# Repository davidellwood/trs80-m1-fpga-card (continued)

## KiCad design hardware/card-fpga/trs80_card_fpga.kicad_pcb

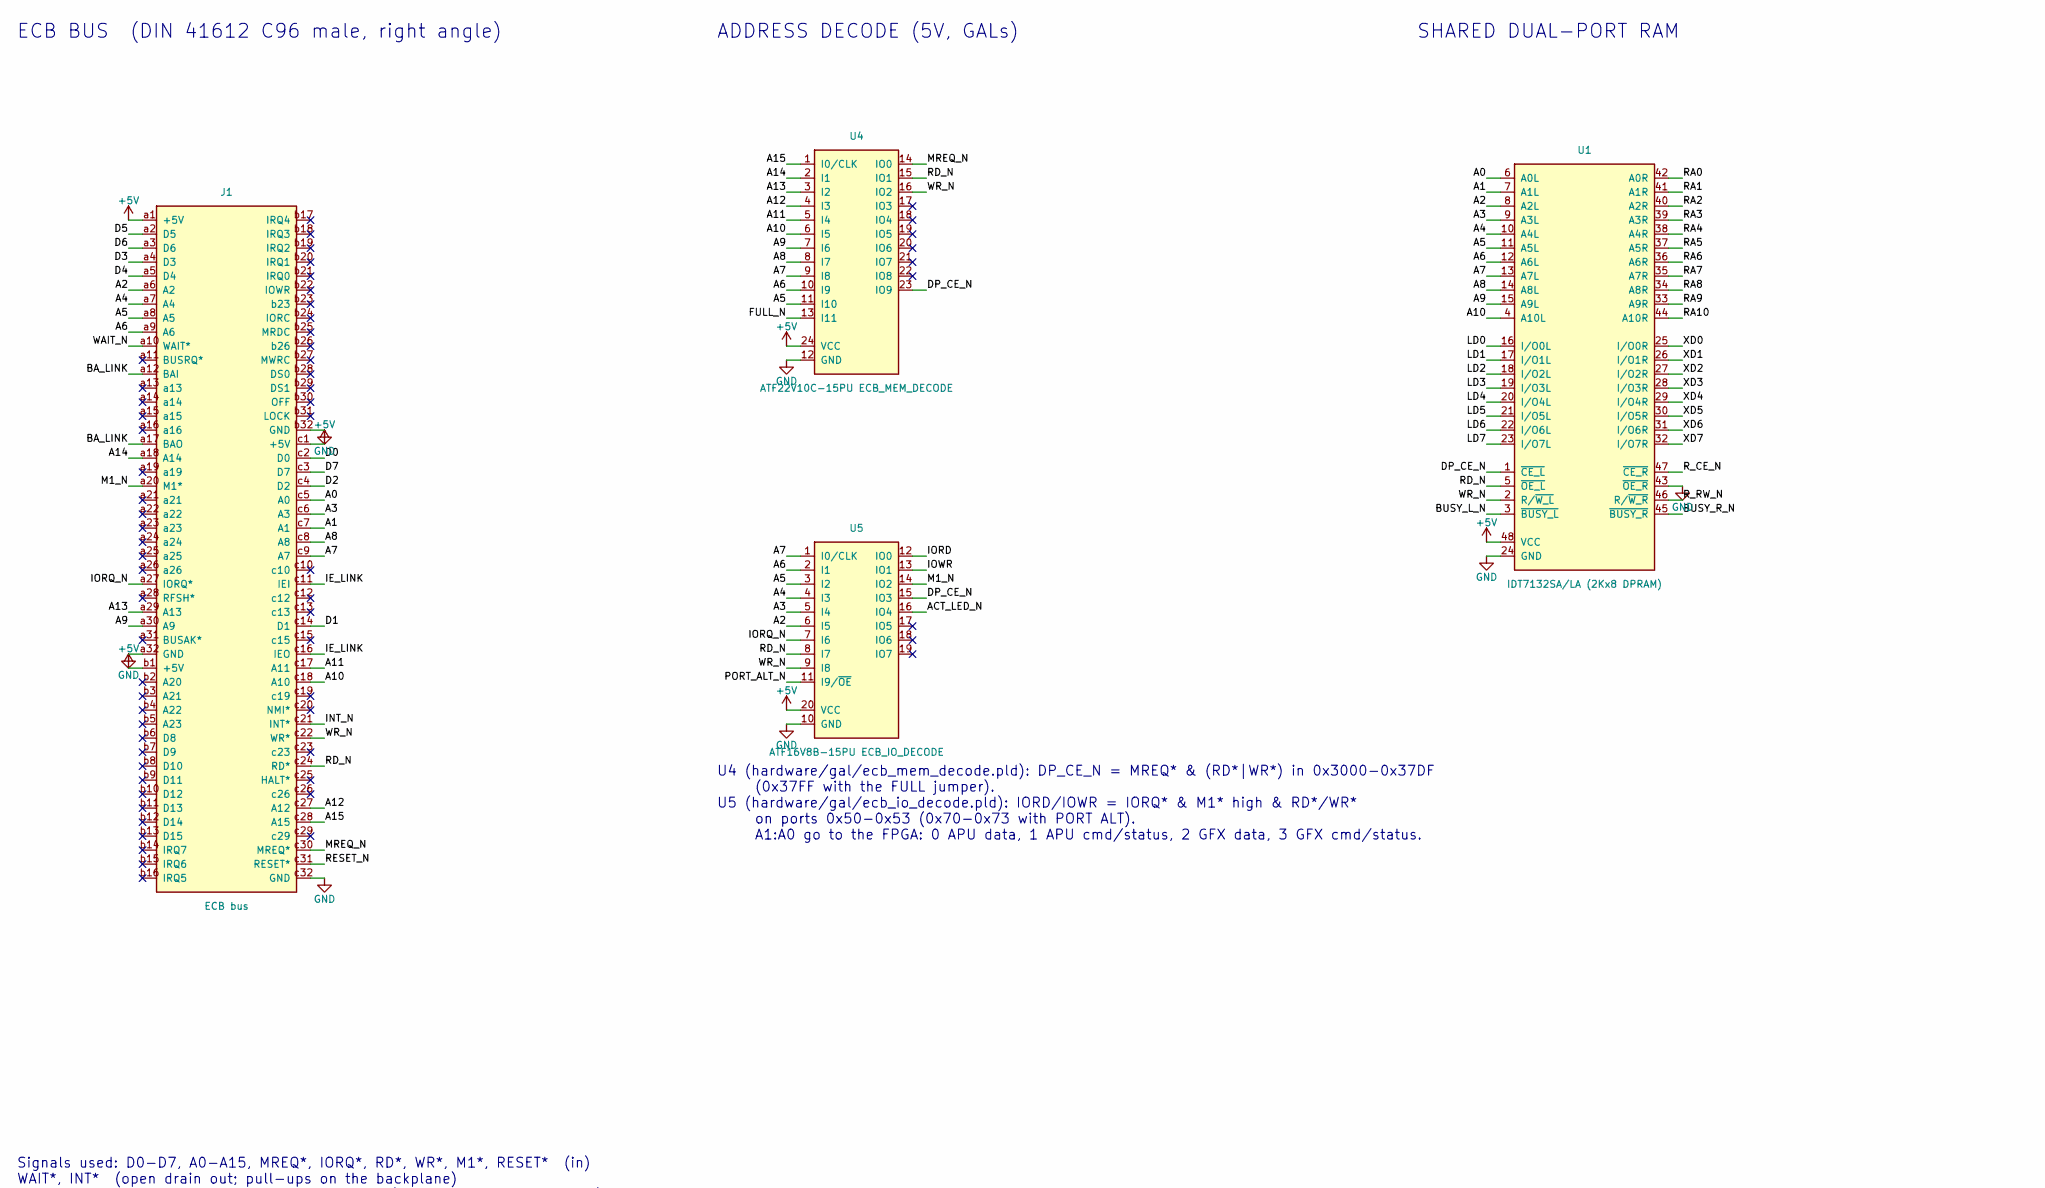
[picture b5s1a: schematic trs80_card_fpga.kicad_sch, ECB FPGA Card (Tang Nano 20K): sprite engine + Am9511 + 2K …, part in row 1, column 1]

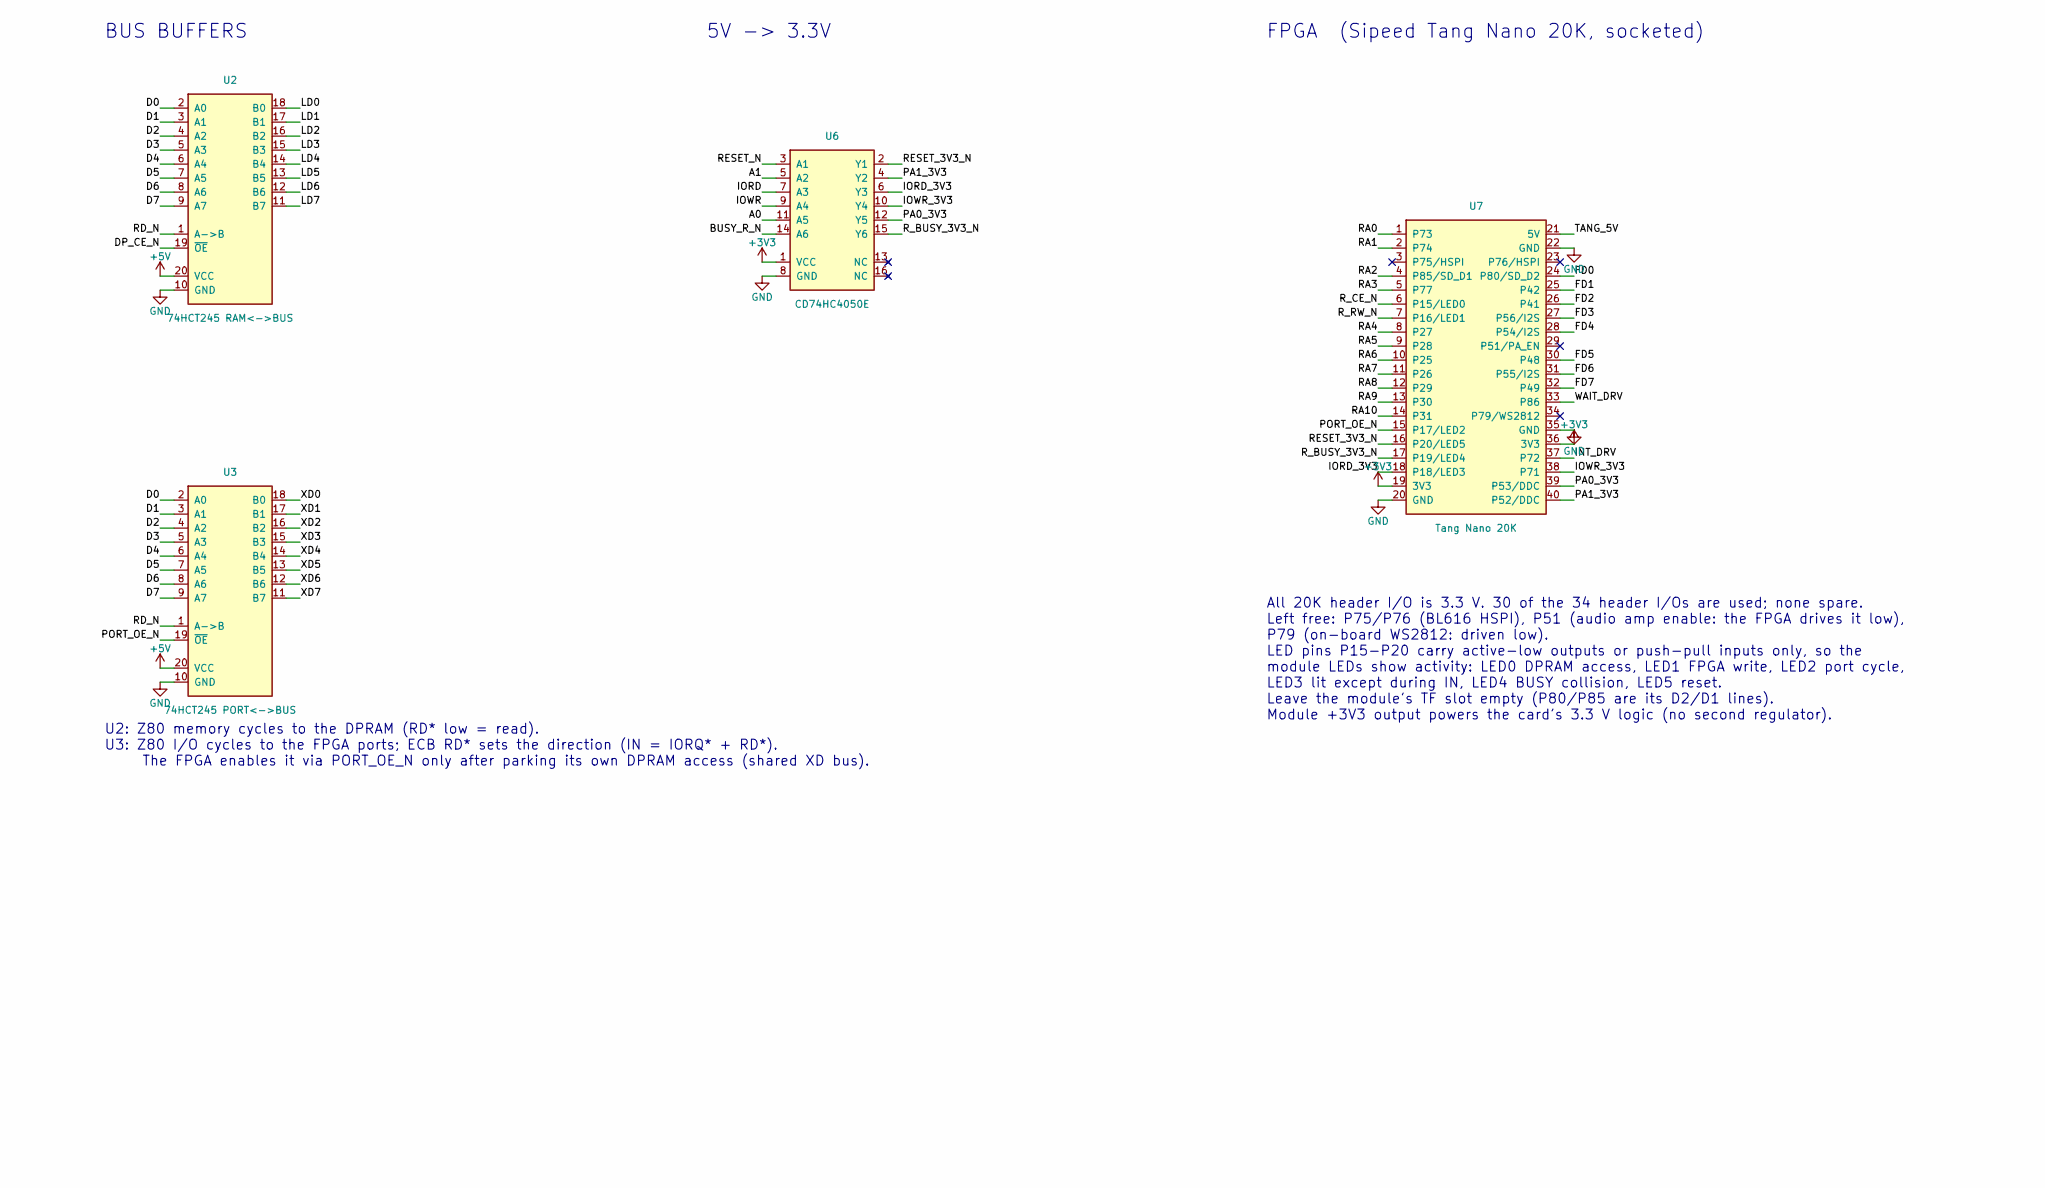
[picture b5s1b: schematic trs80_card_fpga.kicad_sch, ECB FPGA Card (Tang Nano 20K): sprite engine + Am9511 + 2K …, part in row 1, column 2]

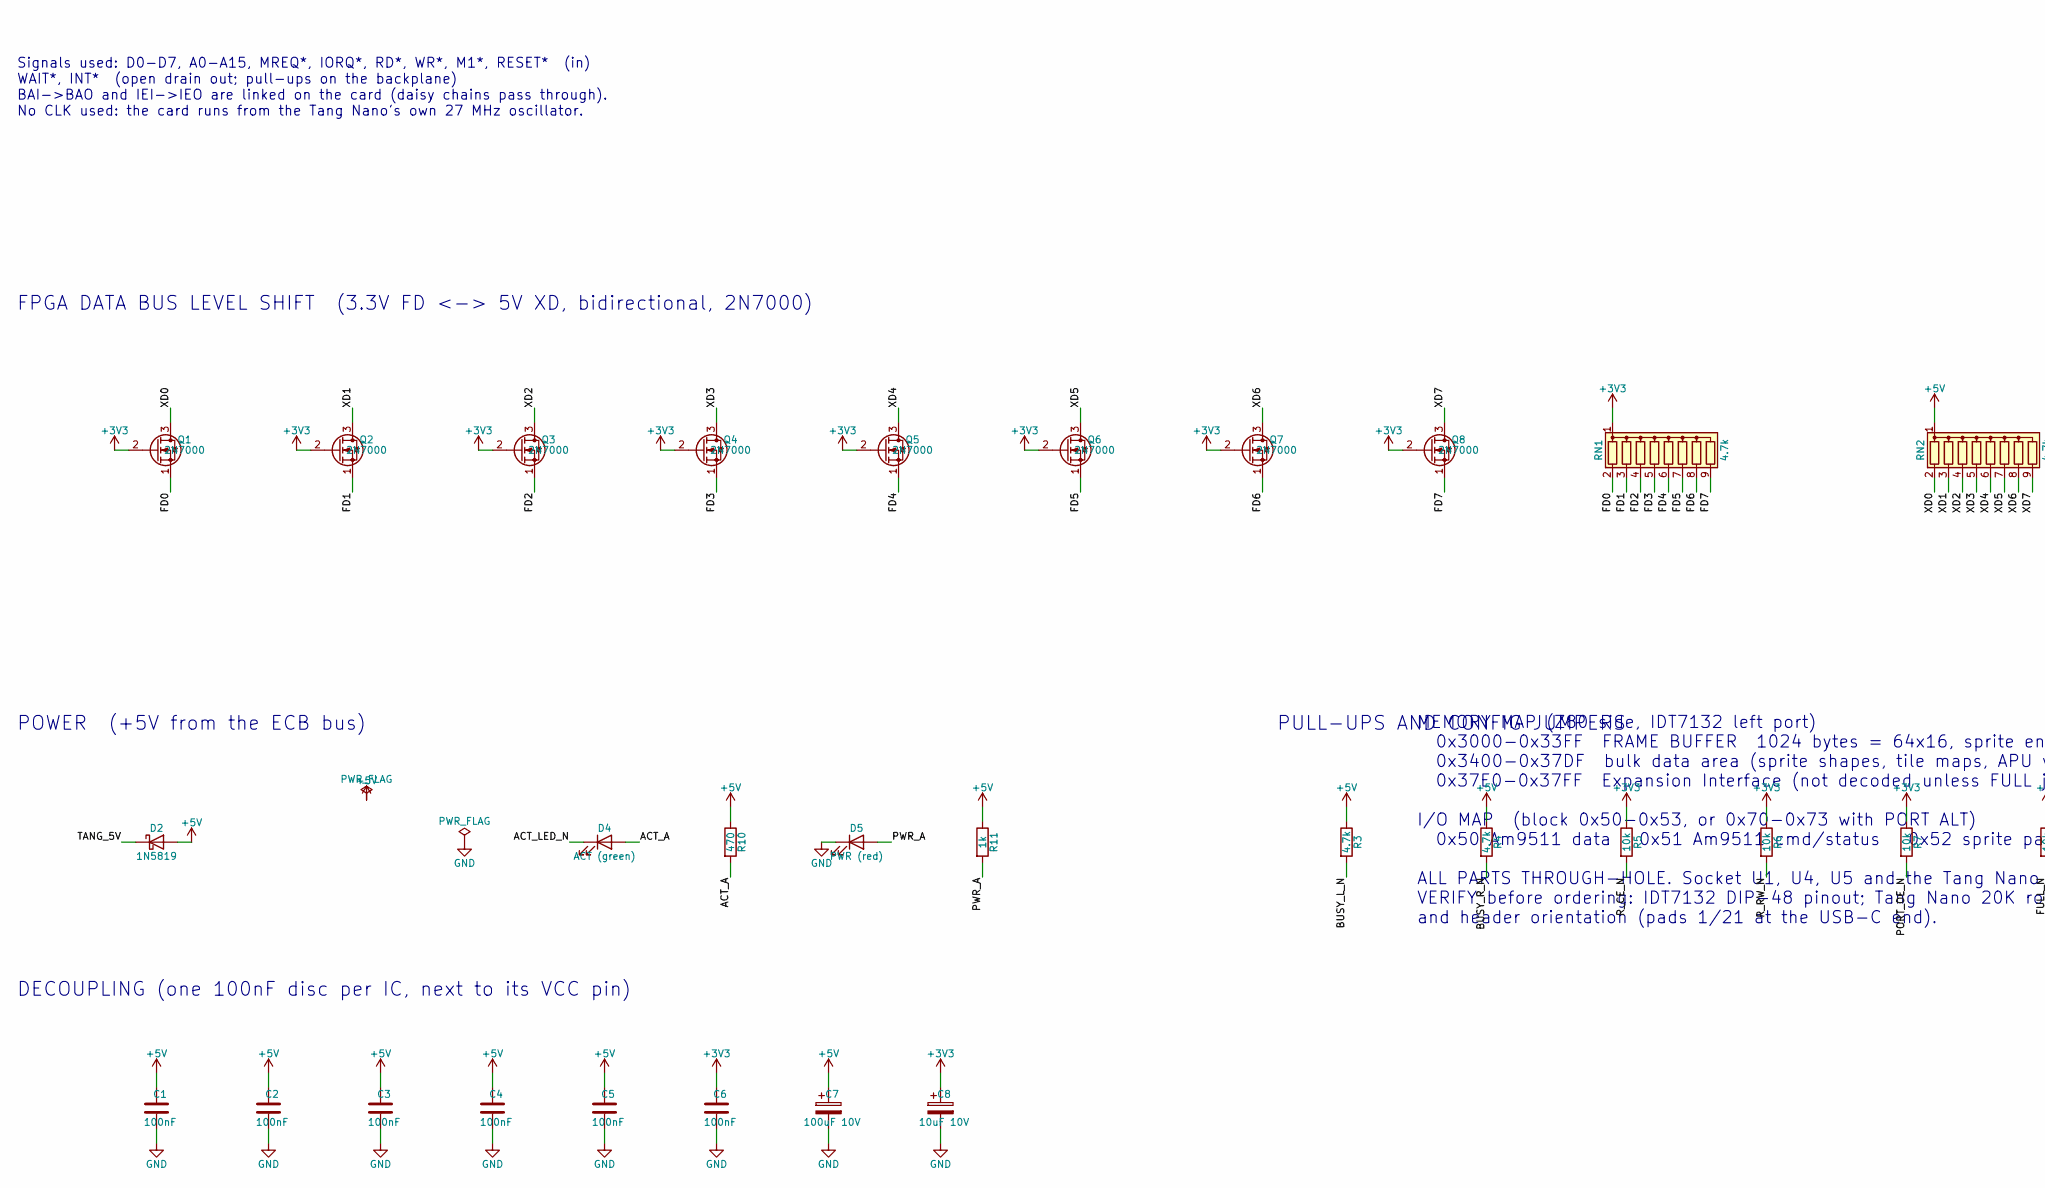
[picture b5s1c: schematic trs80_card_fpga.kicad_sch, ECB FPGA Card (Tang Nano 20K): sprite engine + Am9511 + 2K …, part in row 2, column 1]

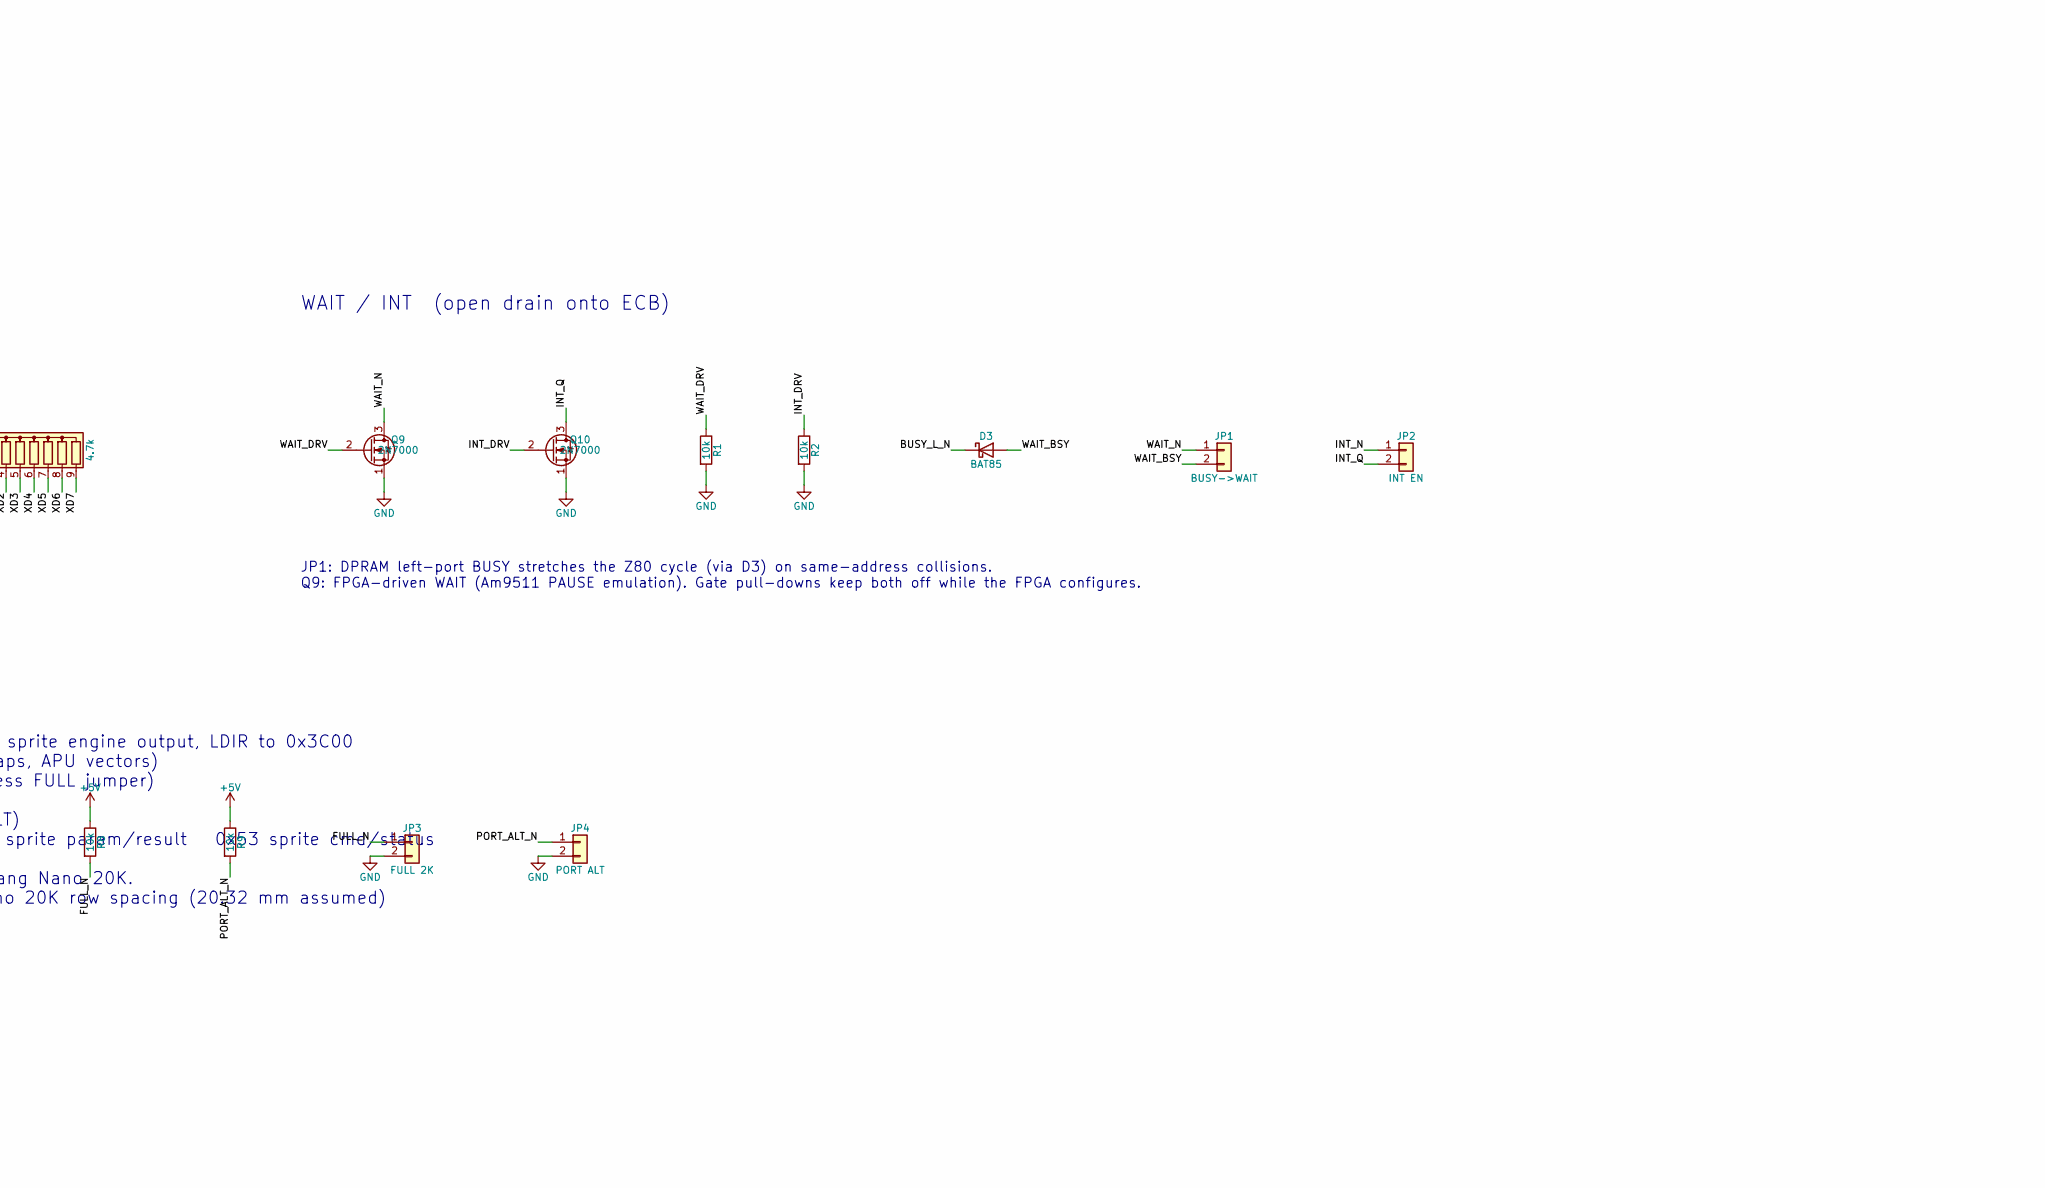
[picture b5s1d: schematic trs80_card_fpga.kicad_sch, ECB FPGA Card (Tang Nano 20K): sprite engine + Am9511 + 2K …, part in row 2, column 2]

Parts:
C1, C2, C3, C4, C5, C6: 100nF; C_Disc_D5.0mm_W2.5mm_P5.00mm
C7: 100uF 10V; CP_Radial_D6.3mm_P2.50mm
C8: 10uF 10V; CP_Radial_D6.3mm_P2.50mm
D2: 1N5819; D_DO-41_SOD81_P10.16mm_Horizontal
D3: BAT85; D_DO-35_SOD27_P7.62mm_Horizontal
D4: ACT (green); LED_D3.0mm
D5: PWR (red); LED_D3.0mm
J1: ECB bus; DIN41612_C_3x32_Male_Horizontal_THT
JP1: BUSY->WAIT; PinHeader_1x02_P2.54mm_Vertical
JP2: INT EN; PinHeader_1x02_P2.54mm_Vertical
JP3: FULL 2K; PinHeader_1x02_P2.54mm_Vertical
JP4: PORT ALT; PinHeader_1x02_P2.54mm_Vertical
Q1, Q2, Q3, Q4, Q5, Q6, Q7, Q8, Q9, Q10: 2N7000; TO-92_Inline_Wide
R1, R2, R5, R6, R7, R8, R9: 10k; R_Axial_DIN0207_L6.3mm_D2.5mm_P10.16mm_Horizontal
R3, R4: 4.7k; R_Axial_DIN0207_L6.3mm_D2.5mm_P10.16mm_Horizontal
R10: 470; R_Axial_DIN0207_L6.3mm_D2.5mm_P10.16mm_Horizontal
R11: 1k; R_Axial_DIN0207_L6.3mm_D2.5mm_P10.16mm_Horizontal
RN1, RN2: 4.7k; R_Array_SIP9
U1: IDT7132SA/LA (2Kx8 DPRAM); DIP-48_W15.24mm_Socket
U2: 74HCT245 RAM<->BUS; DIP-20_W7.62mm
U3: 74HCT245 PORT<->BUS; DIP-20_W7.62mm
U4: ATF22V10C-15PU ECB_MEM_DECODE; DIP-24_W7.62mm_Socket
U5: ATF16V8B-15PU ECB_IO_DECODE; DIP-20_W7.62mm_Socket
U6: CD74HC4050E; DIP-16_W7.62mm
U7: Tang Nano 20K; TangNano20K_2x20_W20.32mm

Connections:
+3V3: C6.1, C8.1, Q1.2 (G), Q2.2 (G), Q3.2 (G), Q4.2 (G), Q5.2 (G), Q6.2 (G), Q7.2 (G), Q8.2 (G), R5.1, R6.1, R7.1, RN1.1 (common), U6.1 (VCC), U7.19 (3V3), U7.36 (3V3)
+5V: C1.1, C2.1, C3.1, C4.1, C5.1, C7.1, D2.2 (A), J1.a1 (+5V), J1.b1 (+5V), J1.c1 (+5V), R3.1, R4.1, R8.1, R9.1, R10.1, R11.1, RN2.1 (common), U1.48 (VCC), U2.20 (VCC), U3.20 (VCC), U4.24 (VCC), U5.20 (VCC)
/A0: J1.c5 (A0), U1.6 (A0L), U6.11 (A5)
/A1: J1.c7 (A1), U1.7 (A1L), U6.5 (A2)
/A2: J1.a6 (A2), U1.8 (A2L), U5.6 (I5)
/A3: J1.c6 (A3), U1.9 (A3L), U5.5 (I4)
/A4: J1.a7 (A4), U1.10 (A4L), U5.4 (I3)
/A5: J1.a8 (A5), U1.11 (A5L), U4.11 (I10), U5.3 (I2)
/A6: J1.a9 (A6), U1.12 (A6L), U4.10 (I9), U5.2 (I1)
/A7: J1.c9 (A7), U1.13 (A7L), U4.9 (I8), U5.1 (I0/CLK)
/A8: J1.c8 (A8), U1.14 (A8L), U4.8 (I7)
/A9: J1.a30 (A9), U1.15 (A9L), U4.7 (I6)
/A10: J1.c18 (A10), U1.4 (A10L), U4.6 (I5)
/A11: J1.c17 (A11), U4.5 (I4)
/A12: J1.c27 (A12), U4.4 (I3)
/A13: J1.a29 (A13), U4.3 (I2)
/A14: J1.a18 (A14), U4.2 (I1)
/A15: J1.c28 (A15), U4.1 (I0/CLK)
/ACT_A: D4.2 (A), R10.2
/ACT_LED_N: D4.1 (K), U5.16 (IO4)
/BA_LINK: J1.a12 (BAI), J1.a17 (BAO)
/BUSY_L_N: D3.1 (K), R3.2, U1.3 (~BUSY_L)
/BUSY_R_N: R4.2, U1.45 (~BUSY_R), U6.14 (A6)
/D0: J1.c2 (D0), U2.2 (A0), U3.2 (A0)
/D1: J1.c14 (D1), U2.3 (A1), U3.3 (A1)
/D2: J1.c4 (D2), U2.4 (A2), U3.4 (A2)
/D3: J1.a4 (D3), U2.5 (A3), U3.5 (A3)
/D4: J1.a5 (D4), U2.6 (A4), U3.6 (A4)
/D5: J1.a2 (D5), U2.7 (A5), U3.7 (A5)
/D6: J1.a3 (D6), U2.8 (A6), U3.8 (A6)
/D7: J1.c3 (D7), U2.9 (A7), U3.9 (A7)
/DP_CE_N: U1.1 (~CE_L), U2.19 (~OE), U4.23 (IO9), U5.15 (IO3)
/FD0: Q1.1 (S), RN1.2 (R1), U7.24 (P80/SD_D2)
/FD1: Q2.1 (S), RN1.3 (R2), U7.25 (P42)
/FD2: Q3.1 (S), RN1.4 (R3), U7.26 (P41)
/FD3: Q4.1 (S), RN1.5 (R4), U7.27 (P56/I2S)
/FD4: Q5.1 (S), RN1.6 (R5), U7.28 (P54/I2S)
/FD5: Q6.1 (S), RN1.7 (R6), U7.30 (P48)
/FD6: Q7.1 (S), RN1.8 (R7), U7.31 (P55/I2S)
/FD7: Q8.1 (S), RN1.9 (R8), U7.32 (P49)
/FULL_N: JP3.1, R8.2, U4.13 (I11)
/IE_LINK: J1.c11 (IEI), J1.c16 (IEO)
/INT_DRV: Q10.2 (G), R2.1, U7.37 (P72)
/INT_N: J1.c21 (INT*), JP2.1
/INT_Q: JP2.2, Q10.3 (D)
/IORD: U5.12 (IO0), U6.7 (A3)
/IORD_3V3: U6.6 (Y3), U7.18 (P18/LED3)
/IORQ_N: J1.a27 (IORQ*), U5.7 (I6)
/IOWR: U5.13 (IO1), U6.9 (A4)
/IOWR_3V3: U6.10 (Y4), U7.38 (P71)
/LD0: U1.16 (I/O0L), U2.18 (B0)
/LD1: U1.17 (I/O1L), U2.17 (B1)
/LD2: U1.18 (I/O2L), U2.16 (B2)
/LD3: U1.19 (I/O3L), U2.15 (B3)
/LD4: U1.20 (I/O4L), U2.14 (B4)
/LD5: U1.21 (I/O5L), U2.13 (B5)
/LD6: U1.22 (I/O6L), U2.12 (B6)
/LD7: U1.23 (I/O7L), U2.11 (B7)
/M1_N: J1.a20 (M1*), U5.14 (IO2)
/MREQ_N: J1.c30 (MREQ*), U4.14 (IO0)
/PA0_3V3: U6.12 (Y5), U7.39 (P53/DDC)
/PA1_3V3: U6.4 (Y2), U7.40 (P52/DDC)
/PORT_ALT_N: JP4.1, R9.2, U5.11 (I9/~OE)
/PORT_OE_N: R7.2, U3.19 (~OE), U7.15 (P17/LED2)
/PWR_A: D5.2 (A), R11.2
/RA0: U1.42 (A0R), U7.1 (P73)
/RA1: U1.41 (A1R), U7.2 (P74)
/RA2: U1.40 (A2R), U7.4 (P85/SD_D1)
/RA3: U1.39 (A3R), U7.5 (P77)
/RA4: U1.38 (A4R), U7.8 (P27)
/RA5: U1.37 (A5R), U7.9 (P28)
/RA6: U1.36 (A6R), U7.10 (P25)
/RA7: U1.35 (A7R), U7.11 (P26)
/RA8: U1.34 (A8R), U7.12 (P29)
/RA9: U1.33 (A9R), U7.13 (P30)
/RA10: U1.44 (A10R), U7.14 (P31)
/RD_N: J1.c24 (RD*), U1.5 (~OE_L), U2.1 (A->B), U3.1 (A->B), U4.15 (IO1), U5.8 (I7)
/RESET_3V3_N: U6.2 (Y1), U7.16 (P20/LED5)
/RESET_N: J1.c31 (RESET*), U6.3 (A1)
/R_BUSY_3V3_N: U6.15 (Y6), U7.17 (P19/LED4)
/R_CE_N: R5.2, U1.47 (~CE_R), U7.6 (P15/LED0)
/R_RW_N: R6.2, U1.46 (R/~W_R), U7.7 (P16/LED1)
/TANG_5V: D2.1 (K), U7.21 (5V)
/WAIT_BSY: D3.2 (A), JP1.2
/WAIT_DRV: Q9.2 (G), R1.1, U7.33 (P86)
/WAIT_N: J1.a10 (WAIT*), JP1.1, Q9.3 (D)
/WR_N: J1.c22 (WR*), U1.2 (R/~W_L), U4.16 (IO2), U5.9 (I8)
/XD0: Q1.3 (D), RN2.2 (R1), U1.25 (I/O0R), U3.18 (B0)
/XD1: Q2.3 (D), RN2.3 (R2), U1.26 (I/O1R), U3.17 (B1)
/XD2: Q3.3 (D), RN2.4 (R3), U1.27 (I/O2R), U3.16 (B2)
/XD3: Q4.3 (D), RN2.5 (R4), U1.28 (I/O3R), U3.15 (B3)
/XD4: Q5.3 (D), RN2.6 (R5), U1.29 (I/O4R), U3.14 (B4)
/XD5: Q6.3 (D), RN2.7 (R6), U1.30 (I/O5R), U3.13 (B5)
/XD6: Q7.3 (D), RN2.8 (R7), U1.31 (I/O6R), U3.12 (B6)
/XD7: Q8.3 (D), RN2.9 (R8), U1.32 (I/O7R), U3.11 (B7)
GND: C1.2, C2.2, C3.2, C4.2, C5.2, C6.2, C7.2, C8.2, D5.1 (K), J1.a32 (GND), J1.b32 (GND), J1.c32 (GND), JP3.2, JP4.2, Q9.1 (S), Q10.1 (S), R1.2, R2.2, U1.24 (GND), U1.43 (~OE_R), U2.10 (GND), U3.10 (GND), U4.12 (GND), U5.10 (GND), U6.8 (GND), U7.20 (GND), U7.22 (GND), U7.35 (GND)

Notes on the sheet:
ECB BUS (DIN 41612 C96 male, right angle)
Signals used: D0-D7, A0-A15, MREQ*, IORQ*, RD*, WR*, M1*, RESET* (in) WAIT*, INT* (open drain out; pull-ups on the backplane) BAI->BAO and IEI->IEO are linked on the card (daisy chains pass through). No CLK used: the card runs from the Tang Nano's own 27 MHz oscillator.
ADDRESS DECODE (5V, GALs)
U4 (hardware/gal/ecb_mem_decode.pld): DP_CE_N = MREQ* & (RD*|WR*) in 0x3000-0x37DF (0x37FF with the FULL jumper). U5 (hardware/gal/ecb_io_decode.pld): IORD/IOWR = IORQ* & M1* high & RD*/WR* on ports 0x50-0x53 (0x70-0x73 with PORT ALT). A1:A0 go to the FPGA: 0 APU data, 1 APU cmd/status, 2 GFX data,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
SHARED DUAL-PORT RAM
BUS BUFFERS
U2: Z80 memory cycles to the DPRAM (RD* low = read). U3: Z80 I/O cycles to the FPGA ports; ECB RD* sets the direction (IN = IORQ* + RD*). The FPGA enables it via PORT_OE_N only after parking its own DPRAM access (shared XD bus).
5V -> 3.3V
FPGA (Sipeed Tang Nano 20K, socketed)
All 20K header I/O is 3.3 V. 30 of the 34 header I/Os are used; none spare. Left free: P75/P76 (BL616 HSPI), P51 (audio amp enable: the FPGA drives it low), P79 (on-board WS2812: driven low). LED pins P15-P20 carry active-low outputs or push-pull inputs only, so the module LEDs show activity: LED0 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
FPGA DATA BUS LEVEL SHIFT (3.3V FD <-> 5V XD, bidirectional, 2N7000)
WAIT / INT (open drain onto ECB)
JP1: DPRAM left-port BUSY stretches the Z80 cycle (via D3) on same-address collisions. Q9: FPGA-driven WAIT (Am9511 PAUSE emulation). Gate pull-downs keep both off while the FPGA configures.
POWER (+5V from the ECB bus)
PULL-UPS AND CONFIG JUMPERS
DECOUPLING (one 100nF disc per IC, next to its VCC pin)
MEMORY MAP (Z80 side, IDT7132 left port) 0x3000-0x33FF FRAME BUFFER 1024 bytes = 64x16, sprite engine output, LDIR to 0x3C00 0x3400-0x37DF bulk data area (sprite shapes, tile maps, APU vectors) 0x37E0-0x37FF Expansion Interface (not decoded unless FULL jumper) I/O MAP (block 0x50-0x53, or 0x70-0x73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

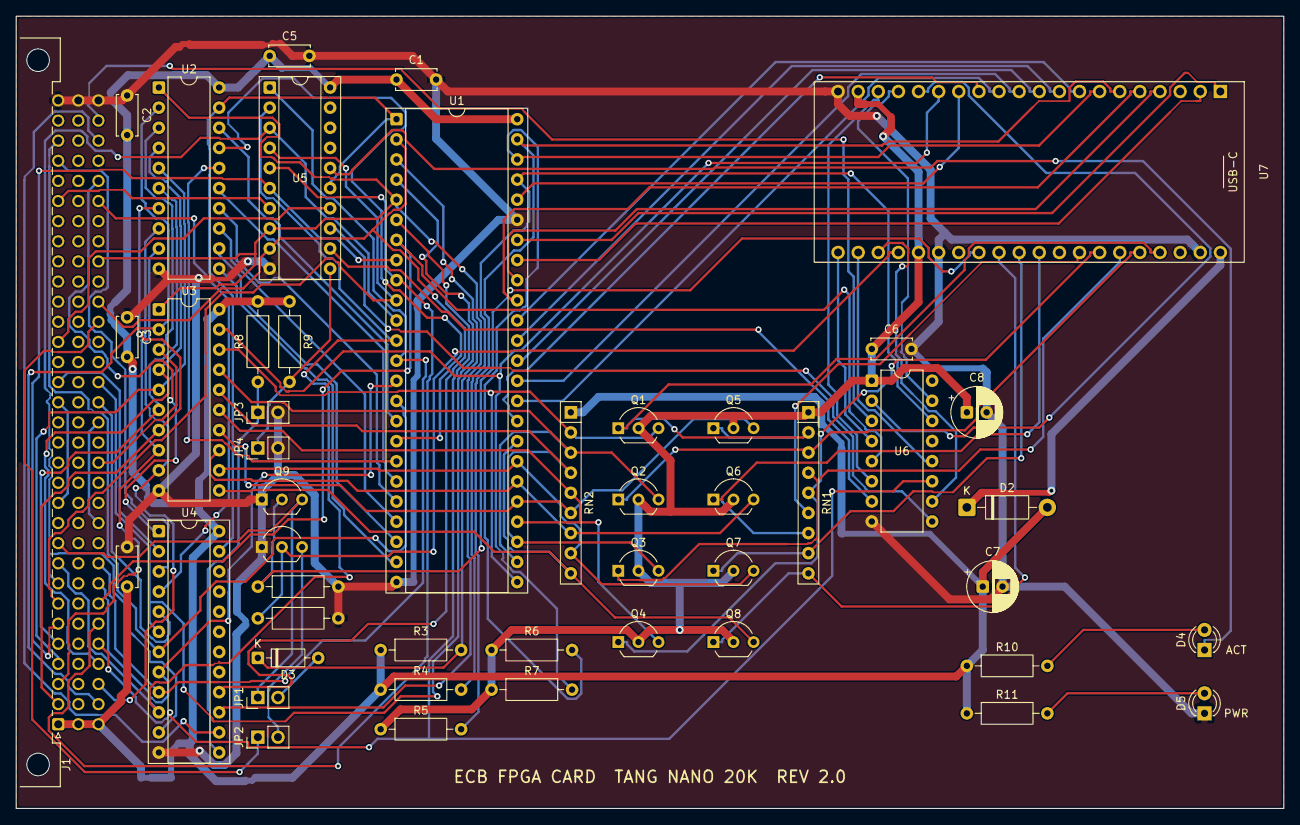
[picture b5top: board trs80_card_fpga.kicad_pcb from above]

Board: 2 copper layers, 160.0 x 100.0 mm, 47 parts (0 on the bottom side), 96 nets.

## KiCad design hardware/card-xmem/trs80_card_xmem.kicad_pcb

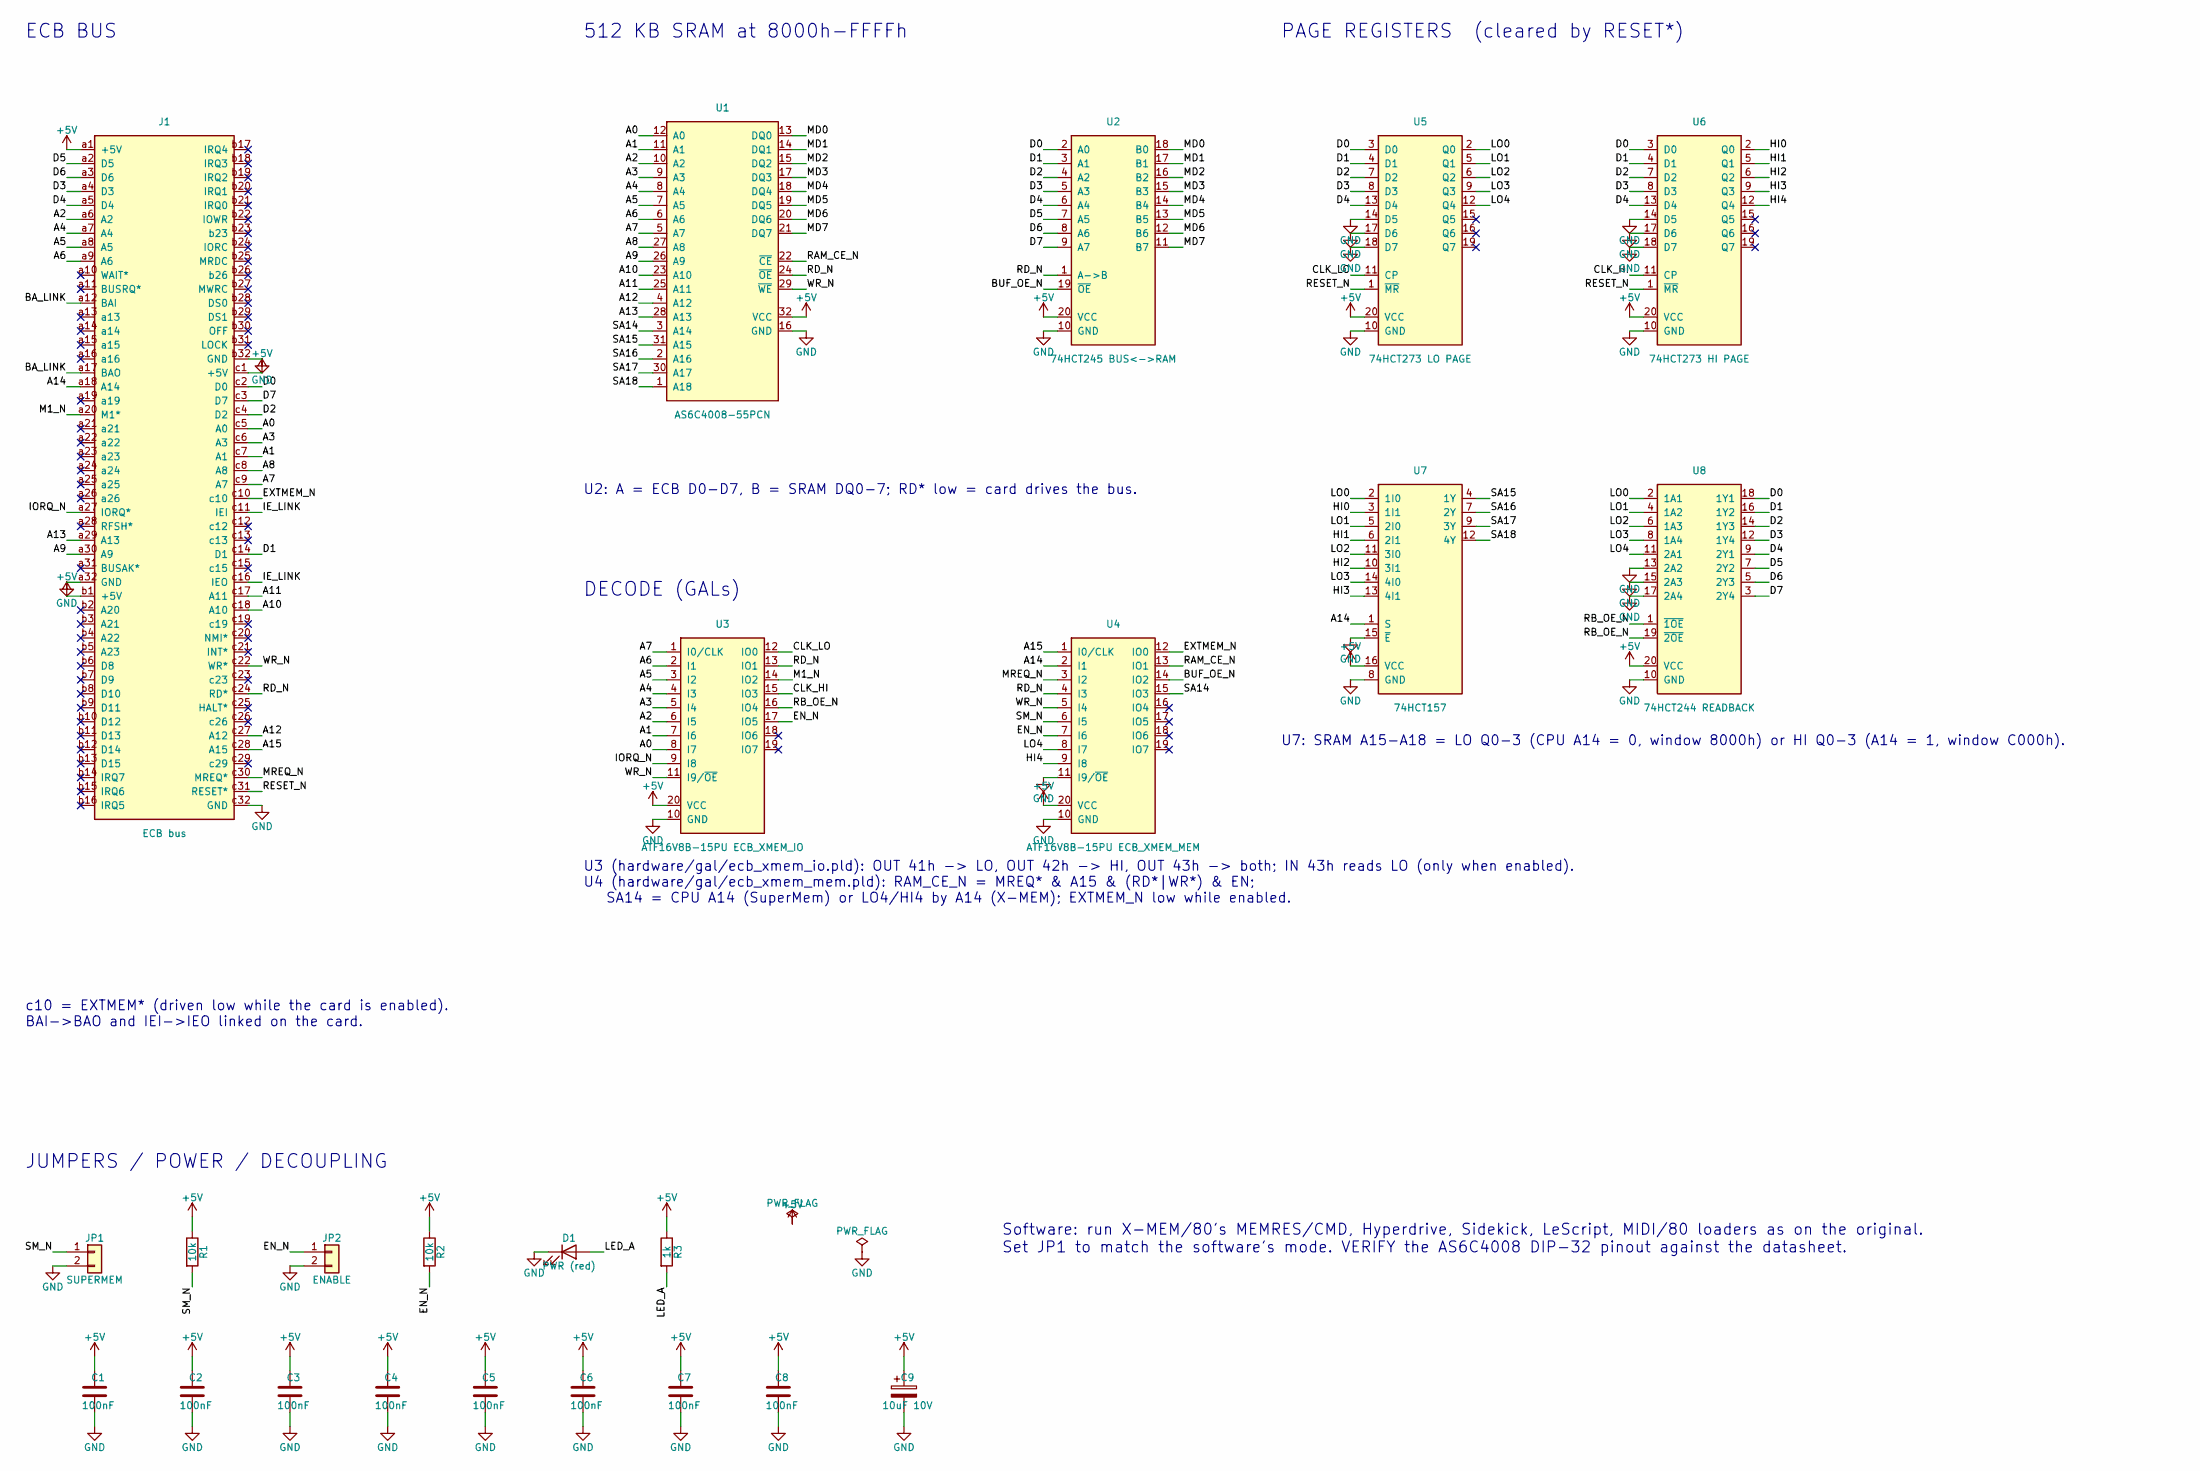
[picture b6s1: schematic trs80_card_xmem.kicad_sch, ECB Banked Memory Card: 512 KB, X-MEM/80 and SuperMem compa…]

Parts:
C1, C2, C3, C4, C5, C6, C7, C8: 100nF; C_Disc_D5.0mm_W2.5mm_P5.00mm
C9: 10uF 10V; CP_Radial_D5.0mm_P2.00mm
D1: PWR (red); LED_D3.0mm
J1: ECB bus; DIN41612_C_3x32_Male_Horizontal_THT
JP1: SUPERMEM; PinHeader_1x02_P2.54mm_Vertical
JP2: ENABLE; PinHeader_1x02_P2.54mm_Vertical
R1, R2: 10k; R_Axial_DIN0207_L6.3mm_D2.5mm_P10.16mm_Horizontal
R3: 1k; R_Axial_DIN0207_L6.3mm_D2.5mm_P10.16mm_Horizontal
U1: AS6C4008-55PCN; DIP-32_W15.24mm_Socket
U2: 74HCT245 BUS<->RAM; DIP-20_W7.62mm
U3: ATF16V8B-15PU ECB_XMEM_IO; DIP-20_W7.62mm_Socket
U4: ATF16V8B-15PU ECB_XMEM_MEM; DIP-20_W7.62mm_Socket
U5: 74HCT273 LO PAGE; DIP-20_W7.62mm
U6: 74HCT273 HI PAGE; DIP-20_W7.62mm
U7: 74HCT157; DIP-16_W7.62mm
U8: 74HCT244 READBACK; DIP-20_W7.62mm

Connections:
+5V: C1.1, C2.1, C3.1, C4.1, C5.1, C6.1, C7.1, C8.1, C9.1, J1.a1 (+5V), J1.b1 (+5V), J1.c1 (+5V), R1.1, R2.1, R3.1, U1.32 (VCC), U2.20 (VCC), U3.20 (VCC), U4.20 (VCC), U5.20 (VCC), U6.20 (VCC), U7.16 (VCC), U8.20 (VCC)
/A0: J1.c5 (A0), U1.12 (A0), U3.8 (I7)
/A1: J1.c7 (A1), U1.11 (A1), U3.7 (I6)
/A2: J1.a6 (A2), U1.10 (A2), U3.6 (I5)
/A3: J1.c6 (A3), U1.9 (A3), U3.5 (I4)
/A4: J1.a7 (A4), U1.8 (A4), U3.4 (I3)
/A5: J1.a8 (A5), U1.7 (A5), U3.3 (I2)
/A6: J1.a9 (A6), U1.6 (A6), U3.2 (I1)
/A7: J1.c9 (A7), U1.5 (A7), U3.1 (I0/CLK)
/A8: J1.c8 (A8), U1.27 (A8)
/A9: J1.a30 (A9), U1.26 (A9)
/A10: J1.c18 (A10), U1.23 (A10)
/A11: J1.c17 (A11), U1.25 (A11)
/A12: J1.c27 (A12), U1.4 (A12)
/A13: J1.a29 (A13), U1.28 (A13)
/A14: J1.a18 (A14), U4.2 (I1), U7.1 (S)
/A15: J1.c28 (A15), U4.1 (I0/CLK)
/BA_LINK: J1.a12 (BAI), J1.a17 (BAO)
/BUF_OE_N: U2.19 (~OE), U4.14 (IO2)
/CLK_HI: U3.15 (IO3), U6.11 (CP)
/CLK_LO: U3.12 (IO0), U5.11 (CP)
/D0: J1.c2 (D0), U2.2 (A0), U5.3 (D0), U6.3 (D0), U8.18 (1Y1)
/D1: J1.c14 (D1), U2.3 (A1), U5.4 (D1), U6.4 (D1), U8.16 (1Y2)
/D2: J1.c4 (D2), U2.4 (A2), U5.7 (D2), U6.7 (D2), U8.14 (1Y3)
/D3: J1.a4 (D3), U2.5 (A3), U5.8 (D3), U6.8 (D3), U8.12 (1Y4)
/D4: J1.a5 (D4), U2.6 (A4), U5.13 (D4), U6.13 (D4), U8.9 (2Y1)
/D5: J1.a2 (D5), U2.7 (A5), U8.7 (2Y2)
/D6: J1.a3 (D6), U2.8 (A6), U8.5 (2Y3)
/D7: J1.c3 (D7), U2.9 (A7), U8.3 (2Y4)
/EN_N: JP2.1, R2.2, U3.17 (IO5), U4.7 (I6)
/EXTMEM_N: J1.c10, U4.12 (IO0)
/HI0: U6.2 (Q0), U7.3 (1I1)
/HI1: U6.5 (Q1), U7.6 (2I1)
/HI2: U6.6 (Q2), U7.10 (3I1)
/HI3: U6.9 (Q3), U7.13 (4I1)
/HI4: U4.9 (I8), U6.12 (Q4)
/IE_LINK: J1.c11 (IEI), J1.c16 (IEO)
/IORQ_N: J1.a27 (IORQ*), U3.9 (I8)
/LED_A: D1.2 (A), R3.2
/LO0: U5.2 (Q0), U7.2 (1I0), U8.2 (1A1)
/LO1: U5.5 (Q1), U7.5 (2I0), U8.4 (1A2)
/LO2: U5.6 (Q2), U7.11 (3I0), U8.6 (1A3)
/LO3: U5.9 (Q3), U7.14 (4I0), U8.8 (1A4)
/LO4: U4.8 (I7), U5.12 (Q4), U8.11 (2A1)
/M1_N: J1.a20 (M1*), U3.14 (IO2)
/MD0: U1.13 (DQ0), U2.18 (B0)
/MD1: U1.14 (DQ1), U2.17 (B1)
/MD2: U1.15 (DQ2), U2.16 (B2)
/MD3: U1.17 (DQ3), U2.15 (B3)
/MD4: U1.18 (DQ4), U2.14 (B4)
/MD5: U1.19 (DQ5), U2.13 (B5)
/MD6: U1.20 (DQ6), U2.12 (B6)
/MD7: U1.21 (DQ7), U2.11 (B7)
/MREQ_N: J1.c30 (MREQ*), U4.3 (I2)
/RAM_CE_N: U1.22 (~CE), U4.13 (IO1)
/RB_OE_N: U3.16 (IO4), U8.1 (~1OE), U8.19 (~2OE)
/RD_N: J1.c24 (RD*), U1.24 (~OE), U2.1 (A->B), U3.13 (IO1), U4.4 (I3)
/RESET_N: J1.c31 (RESET*), U5.1 (~MR), U6.1 (~MR)
/SA14: U1.3 (A14), U4.15 (IO3)
/SA15: U1.31 (A15), U7.4 (1Y)
/SA16: U1.2 (A16), U7.7 (2Y)
/SA17: U1.30 (A17), U7.9 (3Y)
/SA18: U1.1 (A18), U7.12 (4Y)
/SM_N: JP1.1, R1.2, U4.6 (I5)
/WR_N: J1.c22 (WR*), U1.29 (~WE), U3.11 (I9/~OE), U4.5 (I4)
GND: C1.2, C2.2, C3.2, C4.2, C5.2, C6.2, C7.2, C8.2, C9.2, D1.1 (K), J1.a32 (GND), J1.b32 (GND), J1.c32 (GND), JP1.2, JP2.2, U1.16 (GND), U2.10 (GND), U3.10 (GND), U4.10 (GND), U4.11 (I9/~OE), U5.10 (GND), U5.14 (D5), U5.17 (D6), U5.18 (D7), U6.10 (GND), U6.14 (D5), U6.17 (D6), U6.18 (D7), U7.8 (GND), U7.15 (~E), U8.10 (GND), U8.13 (2A2), U8.15 (2A3), U8.17 (2A4)

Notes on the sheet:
ECB BUS
c10 = EXTMEM* (driven low while the card is enabled). BAI->BAO and IEI->IEO linked on the card.
512 KB SRAM at 8000h-FFFFh
U2: A = ECB D0-D7, B = SRAM DQ0-7; RD* low = card drives the bus.
DECODE (GALs)
U3 (hardware/gal/ecb_xmem_io.pld): OUT 41h -> LO, OUT 42h -> HI, OUT 43h -> both; IN 43h reads LO (only when enabled). U4 (hardware/gal/ecb_xmem_mem.pld): RAM_CE_N = MREQ* & A15 & (RD*|WR*) & EN; SA14 = CPU A14 (SuperMem) or LO4/HI4 by A14 (X-MEM); EXTMEM_N low while enabled.
PAGE REGISTERS (cleared by RESET*)
U7: SRAM A15-A18 = LO Q0-3 (CPU A14 = 0, window 8000h) or HI Q0-3 (A14 = 1, window C000h).
JUMPERS / POWER / DECOUPLING
Software: run X-MEM/80's MEMRES/CMD, Hyperdrive, Sidekick, LeScript, MIDI/80 loaders as on the original. Set JP1 to match the software's mode. VERIFY the AS6C4008 DIP-32 pinout against the datasheet.

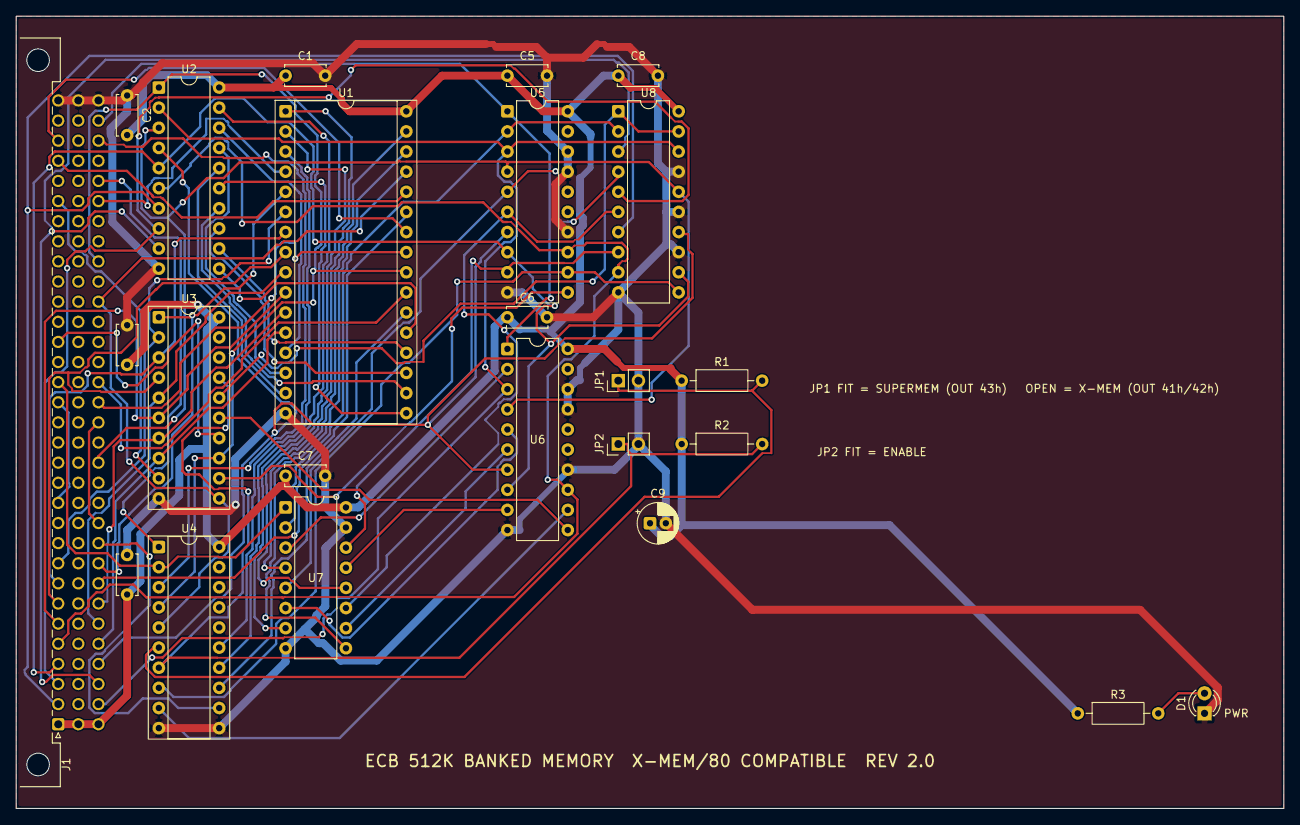
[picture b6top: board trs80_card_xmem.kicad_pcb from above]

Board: 2 copper layers, 160.0 x 100.0 mm, 24 parts (0 on the bottom side), 66 nets.
